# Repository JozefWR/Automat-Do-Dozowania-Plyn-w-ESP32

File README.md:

# Automat do Dozowania Płynów z Obsługą Zdalną (ESP32_BT)

## Opis projektu

Automat do dozowania płynów z możliwością obsługi zdalnej to zaawansowany projekt inżynierski, który łączy w sobie elektronikę i programowanie do stworzenia zintegrowanego systemu sterowania. Projekt został wykonany na Politechnice Koszalińskiej jako praca dyplomowa.

## Instalacja i konfiguracja

1. Sklonuj to repozytorium na swoje lokalne środowisko.
2. Zapoznaj się z dokumentacją techniczną zawartą w pliku `praca_inzynierska.pdf` dla szczegółów dotyczących budowy i działania urządzenia.
3. Zainstaluj wymagane oprogramowanie i biblioteki, jak opisano w dokumentacji.

## Schematy montażu i testowania

Nazwy elementów, moduły, zdjęcia i schematy montażu oraz testowania znajdują się w pliku `praca_inzynierska.pdf`. Wizualizacje te pomogą w zrozumieniu dokładnego procesu składania urządzenia i jego konfiguracji.

## Programowanie

Programowanie mikrokontrolera ESP32 odbywa się przez Arduino IDE. Kod źródłowy oraz szczegółowe instrukcje znajdują się w folderze i pliku `program_ESP32`.

## Zdjęcia i rysunki

-  - zdjęcie gotowego prototypu urządzenia.
-  - schemat komunikacji.
-  - schemat elektroniczny płytki PCB.
- 
 - płytka PCB.
-  - schemat blokowy działania automatu.
- 

- zrzuty ekranu z aplikacji mobilnej.

## Wykorzystane technologie

Projekt wykorzystuje następujące technologie:
- **Mikrokontroler ESP32**: Serce systemu, odpowiada za sterowanie działaniem urządzenia i komunikację zdalną.
- **Arduino IDE**: Środowisko programistyczne używane do pisania kodu dla mikrokontrolera.
- **Eagle CAD**: Oprogramowanie do projektowania płytek PCB, używane do tworzenia schematów elektronicznych i layoutów PCB.
- **Technologie mobilne**: Aplikacja mobilna umożliwia zdalne sterowanie urządzeniem i monitorowanie jego stanu.
- **Bluetooth**: Komunikacja bezprzewodowa między mikrokontrolerem a aplikacją mobilną.

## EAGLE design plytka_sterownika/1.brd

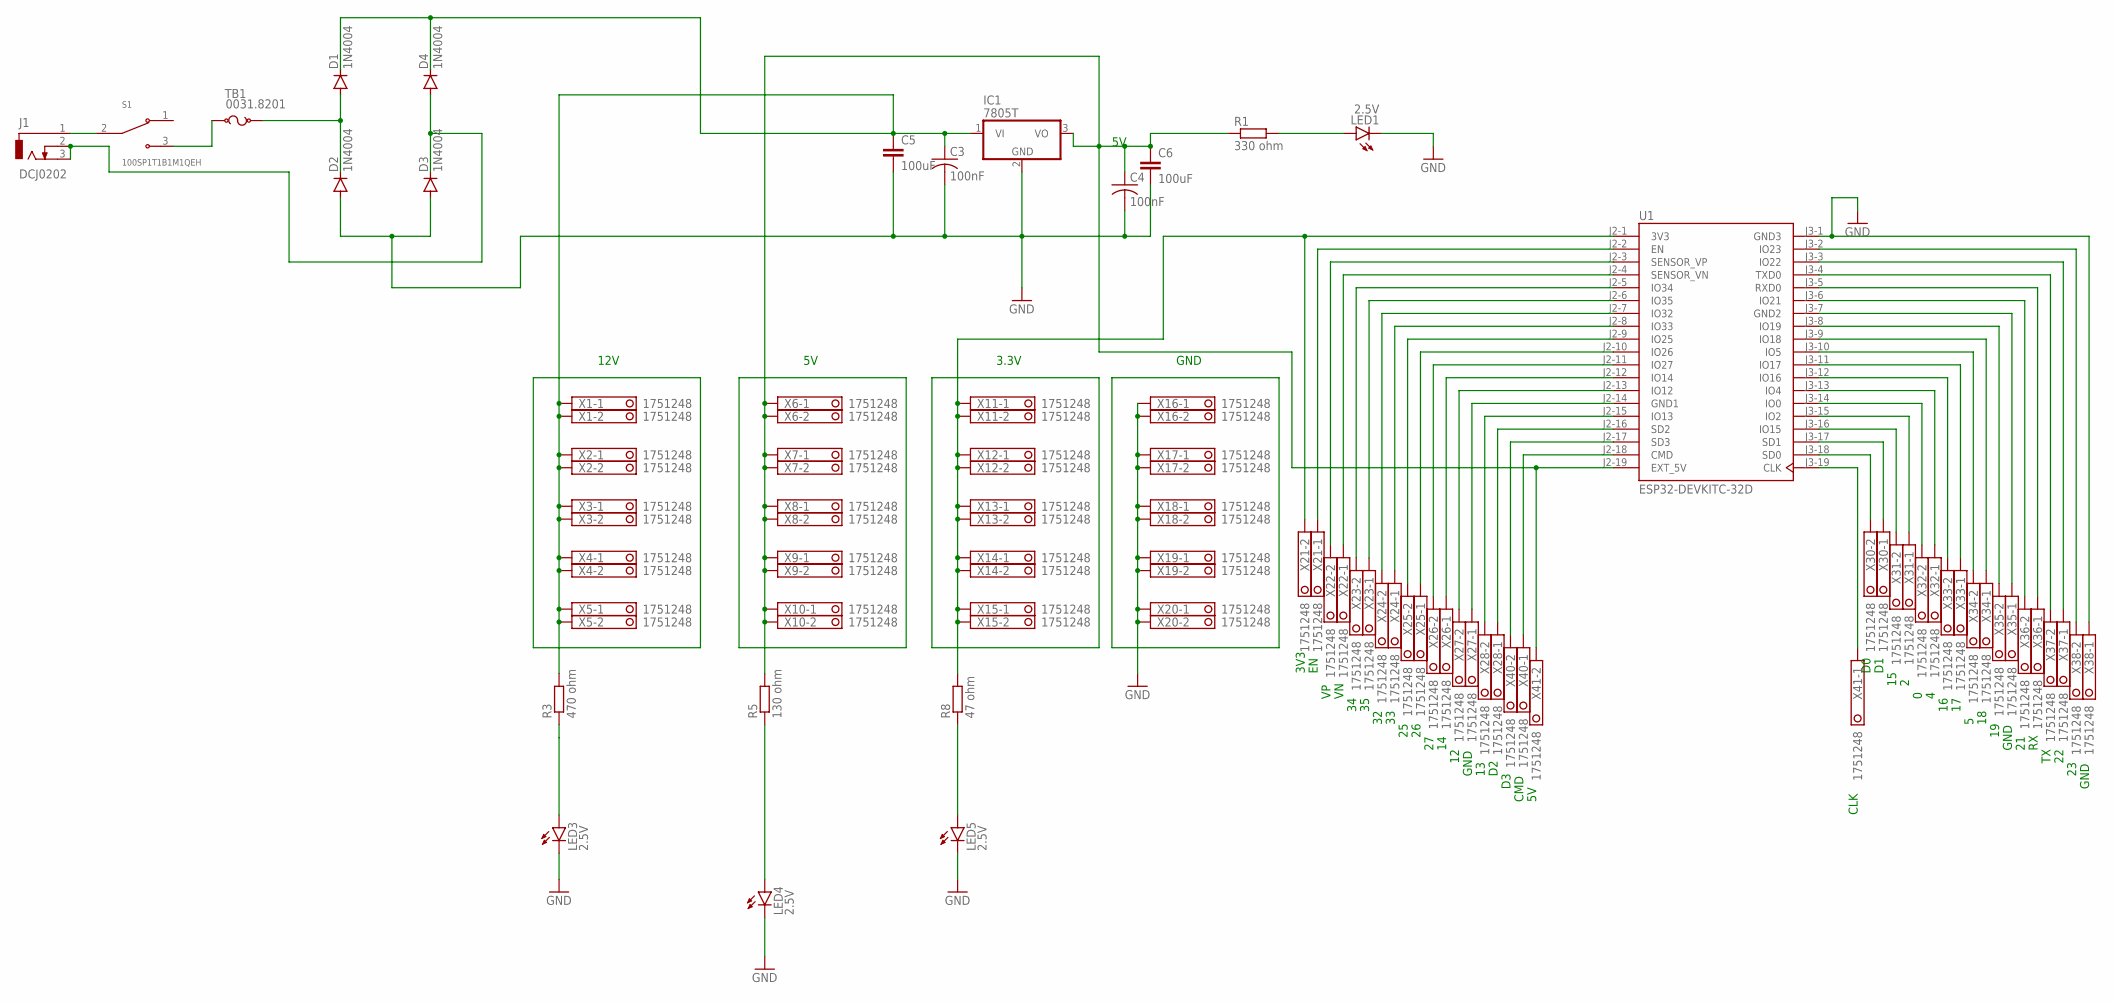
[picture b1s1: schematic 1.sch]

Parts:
C3, C4: 100nF; C025-024X044
C5, C6: 100uF; C025-050X050
D1, D2, D3, D4: 1N4004; DO41-10
IC1: 7805T; TO220H
J1: DCJ0202
LED1, LED3, LED4, LED5: 2.5V; LED3MM
R1: 330 ohm; 0207/10
R3: 470 ohm; 0207/10
R5: 130 ohm; 0207/10
R8: 47 ohm; 0207/10
S1: 100SP1T1B1M1QEH; SW_100SP1T1B1M1QEH
TB1: 0031.8201; SCHURTER_0031.8201
U1: ESP32-DEVKITC-32D; MODULE_ESP32-DEVKITC-32D
X1, X2, X3, X4, X5, X6, X7, X8, X9, X10, X11, X12, X13, X14, X15, X16, X17, X18, X19, X20, X21, X22, X23, X24, X25, X26, X27, X28, X30, X31, X32, X33, X34, X35, X36, X37, X38, X40, X41: 1751248

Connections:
GND: C3.2, C4.2, C5.2, C6.2, D2.A, D3.A, IC1.2 (GND), LED1.K (C), LED3.K (C), LED4.K (C), LED5.K (C), U1.J3-1 (GND3), X16.1, X16.2, X17.1, X17.2, X18.1, X18.2, X19.1, X19.2, X20.1, X20.2, X38.1
unnamed: D3.C, D4.A, J1.2, J1.3
unnamed: C4.1, C6.1, IC1.3 (VO), R1.1, R5.2, U1.J2-19 (EXT_5V), X6.1, X6.2, X7.1, X7.2, X8.1, X8.2, X9.1, X9.2, X10.1, X10.2, X41.2
unnamed: LED1.A, R1.2
unnamed: R8.2, U1.J2-1 (3V3), X11.1, X11.2, X12.1, X12.2, X13.1, X13.2, X14.1, X14.2, X15.1, X15.2, X21.2
unnamed: U1.J2-2 (EN), X21.1
unnamed: U1.J2-3 (SENSOR_VP), X22.2
unnamed: U1.J2-4 (SENSOR_VN), X22.1
unnamed: U1.J2-5 (IO34), X23.2
unnamed: U1.J2-6 (IO35), X23.1
unnamed: U1.J2-7 (IO32), X24.2
unnamed: U1.J2-8 (IO33), X24.1
unnamed: U1.J2-9 (IO25), X25.2
unnamed: U1.J2-10 (IO26), X25.1
unnamed: U1.J2-11 (IO27), X26.2
unnamed: U1.J2-12 (IO14), X26.1
unnamed: U1.J2-13 (IO12), X27.2
unnamed: U1.J2-14 (GND1), X27.1
unnamed: U1.J2-15 (IO13), X28.2
unnamed: U1.J2-16 (SD2), X28.1
unnamed: U1.J2-17 (SD3), X40.2
unnamed: U1.J2-18 (CMD), X40.1
unnamed: U1.J3-19 (CLK), X41.1
unnamed: U1.J3-18 (SD0), X30.2
unnamed: U1.J3-17 (SD1), X30.1
unnamed: U1.J3-16 (IO15), X31.2
unnamed: U1.J3-15 (IO2), X31.1
unnamed: U1.J3-14 (IO0), X32.2
unnamed: U1.J3-13 (IO4), X32.1
unnamed: U1.J3-12 (IO16), X33.2
unnamed: U1.J3-11 (IO17), X33.1
unnamed: U1.J3-10 (IO5), X34.2
unnamed: U1.J3-9 (IO18), X34.1
unnamed: U1.J3-8 (IO19), X35.2
unnamed: U1.J3-7 (GND2), X35.1
unnamed: U1.J3-6 (IO21), X36.2
unnamed: U1.J3-5 (RXD0), X36.1
unnamed: U1.J3-4 (TXD0), X37.2
unnamed: U1.J3-3 (IO22), X37.1
unnamed: U1.J3-2 (IO23), X38.2
unnamed: LED3.A, R3.1
unnamed: D1.A, D2.C, TB1.2
unnamed: S1.3, TB1.1
unnamed: C3.1, C5.1, D1.C, D4.C, IC1.1 (VI), R3.2, X1.1, X1.2, X2.1, X2.2, X3.1, X3.2, X4.1, X4.2, X5.1, X5.2
unnamed: J1.1, S1.2
unnamed: LED4.A, R5.1
unnamed: LED5.A, R8.1

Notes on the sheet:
12V
3.3V
GND
CMD
3V3
CLK

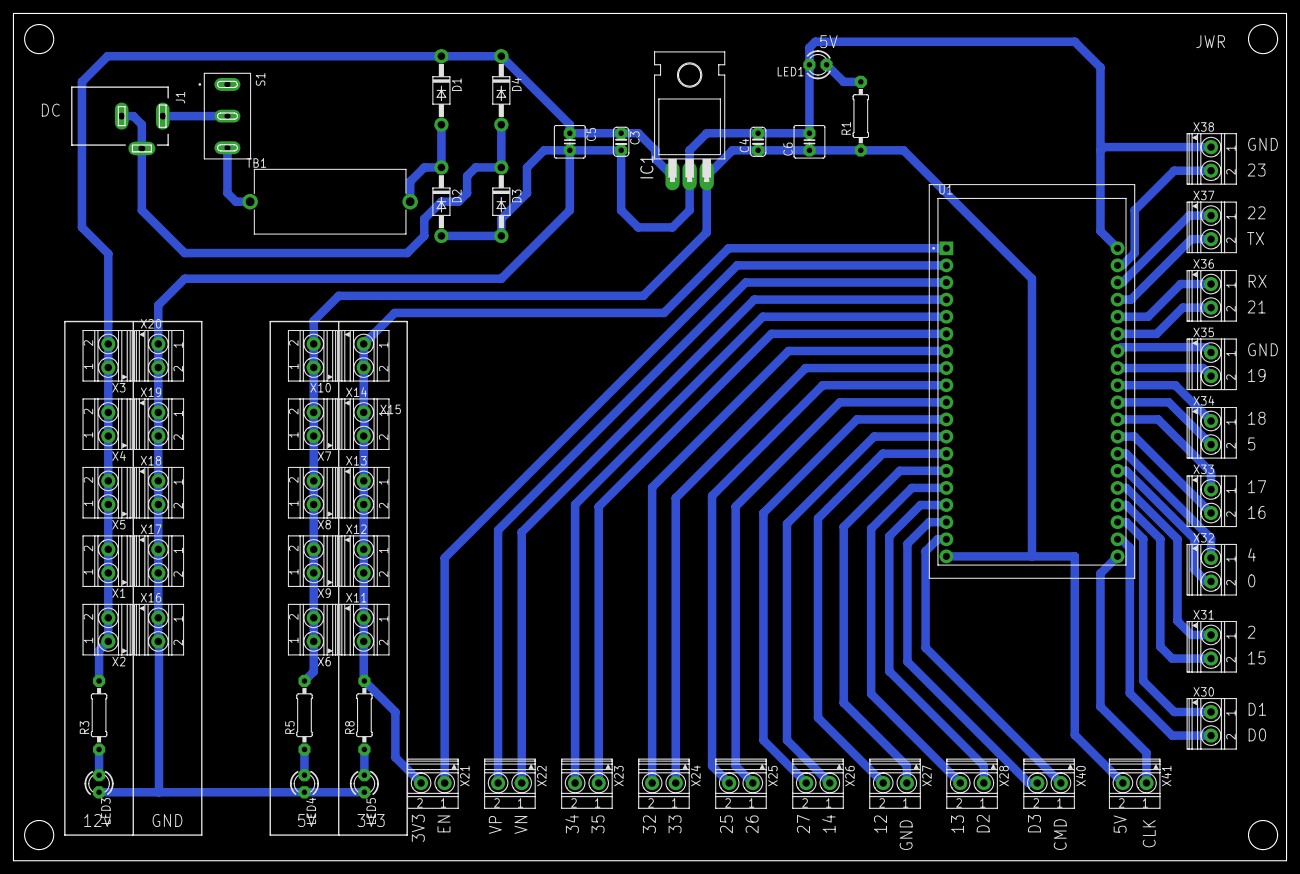
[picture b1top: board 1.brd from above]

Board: 2 copper layers, 188.9 x 125.7 mm, 60 parts (0 on the bottom side), 47 nets.

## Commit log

2024-05-13 Add remaining project files
2024-05-13 README.md
